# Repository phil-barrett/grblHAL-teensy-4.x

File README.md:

# grbl-teensy-4
GRBL Breakout Boards for Teensy 4.x Uses the [grblHAL Teensy 4 version](https://github.com/grblHAL/iMXRT1062).
# Resources for grblHAL, T41U5XBB and related CNC topics
[Resources](https://www.grbl.org/resources)

## Nov 12, 2025.  V2.20 is now available.
Upgraded to AHCT drivers.
Upgraded to EL3H7 optoisolators.
Added board level configuration to support spindle sync. See [user manual](https://github.com/phil-barrett/grblHAL-teensy-4.x/blob/master/T41U5XBB%20User%20Manual.pdf) for details.
.

[Available for purchase on my store.](https://brookwood-design-77.myshopify.com/)

## Aug 20, 2025.  V2.10 is now available.
Trimmer potentiometer moved onto PCB, unneeded features removed and some cosmetic changes.  Now using KiCAD instead of Eagle. V2.11 is coming but is functionally the same as V2.10 (minor slik screen changes).  [User Manual](https://github.com/phil-barrett/grblHAL-teensy-4.x/blob/master/T41U5XBB%20User%20Manual.pdf) updated. 

## Oct 15, 2020.  V2.09 is now available.
A small number of changes, mostly cosmetic. Also added mounting holes for I2C and Serial I/O daughter boards. 

## Sept 29, 2020. Ethernet Support Added
grblHAL support for Ethernet is now pretty solid.  I have updated the [User Manual](https://github.com/phil-barrett/grblHAL-teensy-4.x/blob/master/T41U5XBB%20v207.pdf) to include instructions on using Ethernet. 

## June 28, 2020. New Versions!
I have finished 2 new 5 axis versions based on the Teensy 4.1. One supports an Ethernet interface and the other supports a USB interface. I will be making a few "Unkit" boards avalable. These have all the surface mount components installed (with the execption of the EEPROM IC). Teensy 4.1 not included. 

The "Unkit" board.

T41U5XBB - Fully populated USB based version.  

T41E5XBB - Fully populated Ethernet version

Lots of new features!
## Features
  * 5 Axis control outputs – 5V compatible.
  * Independent enables for each axis.
  * 10 Opto-isolated inputs including standard GRBL controls and limits switches for all axes.
  * 7 Relay Outputs – Spindle, Mist Coolant, Flood Coolant, Dust Collector and 3 auxiliary relays. Each output can control a relay coil directly or 5V TTL (SSR compatible) devices.
  * Dust Extraction relay support. Activated by spindle enable.
  * Separate control of Dust Collector relay via pin header.
  * Relay coil voltage switchable between 5V and 12V. 
  * Standard GRBL spindle control outputs – 5V compliant.
  * 0-10V spindle control output.
  * Screw Terminals for reliable connections available for most I/O.
  * 4 Digital Inputs – EMI protected, 15.9KHz low pass filter, Schmitt Trigger.
  * I2C header.
  * EEPROM footprint for SOIC8 devices.
  * LED indicators for 5V and 12V.
  * USB interface.
  * Ethernet interface. (T41E5XBB only)
  * Serial I/O Header

## Firmware
Prebuilt versions of grblHAL are available to directly load into the Teensy 4.1 [Follow the instructions here.](https://github.com/phil-barrett/grblHAL-teensy-4.x/blob/master/prebuilt.md)

## Documentation
### Schematic
The two versions currently share a common schematic and PCB layout. This may not be the case in the future. [Schematic is here.](https://github.com/phil-barrett/grbl-teensy-4/blob/master/v2.07%20schematic.pdf)

### Manual
The [User Manual is available here.](https://github.com/phil-barrett/grbl-teensy-4/blob/master/T41U5XBB%20v207.pdf)

### Bare PCB from OSHPark
[Available here](https://oshpark.com/shared_projects/QWr3OZUe) This is fairly expensive. For a less costly approach, you can use the Gerber files below to order from more cost effective fabs.

### Gerbers
[Gerbers are available here.](https://github.com/phil-barrett/grbl-teensy-4/blob/master/teensy%204.1x207.zip) Board size is 85 x 96 mm, 2 layer, 1.6 mm thickness.

### Build Guide
A brief guide to building grblHAL from source [for the breakout board is here](https://github.com/phil-barrett/grbl-teensy-4/blob/master/grblHAL%20Build%20Guide.pdf).

## Previous Version

## Features:
  * 4 Axis control outputs – 5V Compatible.
  * 8 Opto-isolated inputs.
  * Full spindle control outputs – 5V compatible.
  * 0-10V spindle control output.
  * 7 Relay Outputs.
  * Relay voltage switchable between 5V and 12V. 
  * Dust Extraction relay output slaved to spindle.
  * Screw Terminal I/O for reliable connections.
  * I2C header.
  * EEPROM footprint for SOIC8 devices.
  * LED indicators for 5V and 12V.

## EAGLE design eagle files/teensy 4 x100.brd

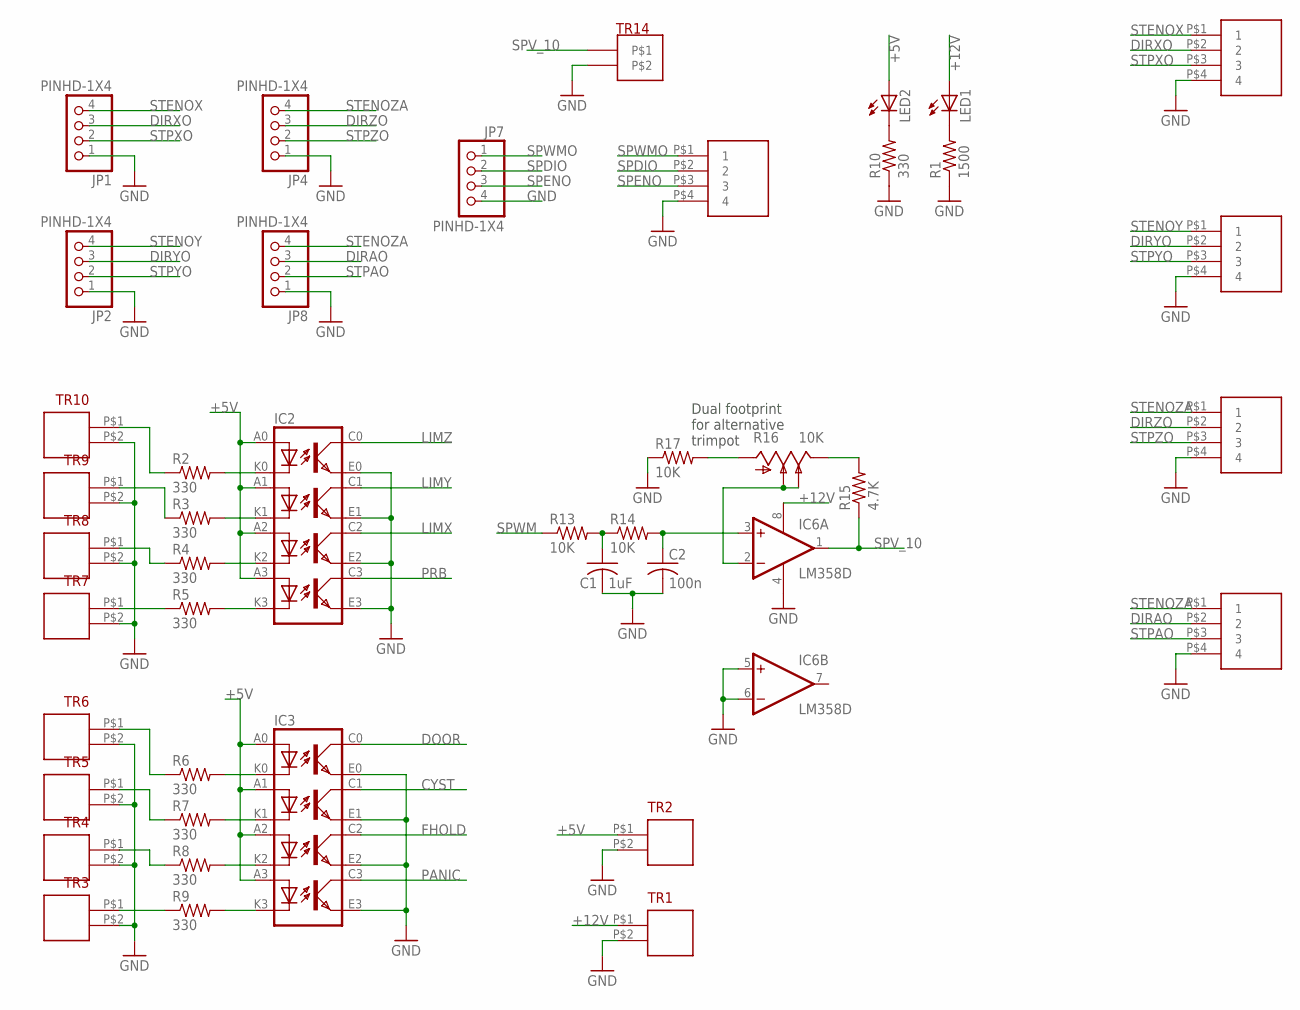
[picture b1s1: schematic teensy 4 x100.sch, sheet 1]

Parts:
C1: 1uF; C1206
C2: 100n; C1206
IC2, IC3: LTV846S; DIL16-SMD
IC6: LM358D; SO08
JP1, JP2, JP4, JP7, JP8: PINHD-1X4; 1X04
LED1, LED2: LED3MM
R1: 1500; R1206
R2, R3, R4, R5, R6, R7, R8, R9, R10: 330; R1206
R13, R14, R17: 10K; R1206
R15: 4.7K; R1206
R16: 10K; B64Y
TR1, TR2, TR3, TR4, TR5, TR6, TR7, TR8, TR9, TR10, TR14: T35-2
TR11, TR12, TR13, TR19, TR20: T35-4

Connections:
+5V: IC2.A0, IC2.A1, IC2.A2, IC2.A3, IC3.A0, IC3.A1, IC3.A2, IC3.A3, LED2.A, TR2.P$1; also elsewhere on the board
+12V: IC6.8 (V+), LED1.A, TR1.P$1; also elsewhere on the board
CYST: IC3.C1 (COL1); also elsewhere on the board
DIRAO: JP8.3, TR20.P$2 (2); also elsewhere on the board
DIRXO: JP1.3, TR11.P$2 (2); also elsewhere on the board
DIRYO: JP2.3, TR12.P$2 (2); also elsewhere on the board
DIRZO: JP4.3, TR13.P$2 (2); also elsewhere on the board
DOOR: IC3.C0 (COL0); also elsewhere on the board
FHOLD: IC3.C2 (COL2); also elsewhere on the board
GND: C1.2, C2.2, IC2.E0 (EMIT0), IC2.E1 (EMIT1), IC2.E2 (EMIT2), IC2.E3 (EMIT3), IC3.E0 (EMIT0), IC3.E1 (EMIT1), IC3.E2 (EMIT2), IC3.E3 (EMIT3), IC6.4 (V-), IC6.5 (+IN), IC6.6 (-IN), JP1.1, JP2.1, JP4.1, JP7.4, JP8.1, R1.1, R10.1, R17.1, TR1.P$2, TR2.P$2, TR3.P$2, TR4.P$2, TR5.P$2, TR6.P$2, TR7.P$2, TR8.P$2, TR9.P$2, TR10.P$2, TR11.P$4 (4), TR12.P$4 (4), TR13.P$4 (4), TR14.P$2, TR19.P$4 (4), TR20.P$4 (4); also elsewhere on the board
LIMX: IC2.C2 (COL2); also elsewhere on the board
LIMY: IC2.C1 (COL1); also elsewhere on the board
LIMZ: IC2.C0 (COL0); also elsewhere on the board
unnamed: IC3.K0 (C0), R6.2
unnamed: LED2.K (C), R10.2
unnamed: IC3.K1 (C1), R7.2
unnamed: LED1.K (C), R1.2
unnamed: IC3.K2 (C2), R8.2
unnamed: IC2.K0 (C0), R2.2
unnamed: IC2.K1 (C1), R3.2
unnamed: IC2.K2 (C2), R4.2
unnamed: IC2.K3 (C3), R5.2
unnamed: IC3.K3 (C3), R9.2
unnamed: C1.1, R13.2, R14.1
unnamed: C2.1, IC6.3 (+IN), R14.2
unnamed: R15.2, R16.E
unnamed: IC6.2 (-IN), R16.S, R16.S1
unnamed: R16.A, R17.2
unnamed: R2.1, TR10.P$1
unnamed: R3.1, TR9.P$1
unnamed: R4.1, TR8.P$1
unnamed: R5.1, TR7.P$1
unnamed: R6.1, TR6.P$1
unnamed: R7.1, TR5.P$1
unnamed: R8.1, TR4.P$1
unnamed: R9.1, TR3.P$1
PANIC: IC3.C3 (COL3); also elsewhere on the board
PRB: IC2.C3 (COL3); also elsewhere on the board
SPDIO: JP7.2, TR19.P$2 (2); also elsewhere on the board
SPENO: JP7.3, TR19.P$3 (3); also elsewhere on the board
SPV_10: IC6.1 (OUT), R15.1, TR14.P$1
SPWM: R13.1; also elsewhere on the board
SPWMO: JP7.1, TR19.P$1 (1); also elsewhere on the board
STENOX: JP1.4, TR11.P$1 (1); also elsewhere on the board
STENOY: JP2.4, TR12.P$1 (1); also elsewhere on the board
STENOZA: JP4.4, JP8.4, TR13.P$1 (1), TR20.P$1 (1); also elsewhere on the board
STPAO: JP8.2, TR20.P$3 (3); also elsewhere on the board
STPXO: JP1.2, TR11.P$3 (3); also elsewhere on the board
STPYO: JP2.2, TR12.P$3 (3); also elsewhere on the board
STPZO: JP4.2, TR13.P$3 (3); also elsewhere on the board

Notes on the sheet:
Dual footprint for alternative trimpot

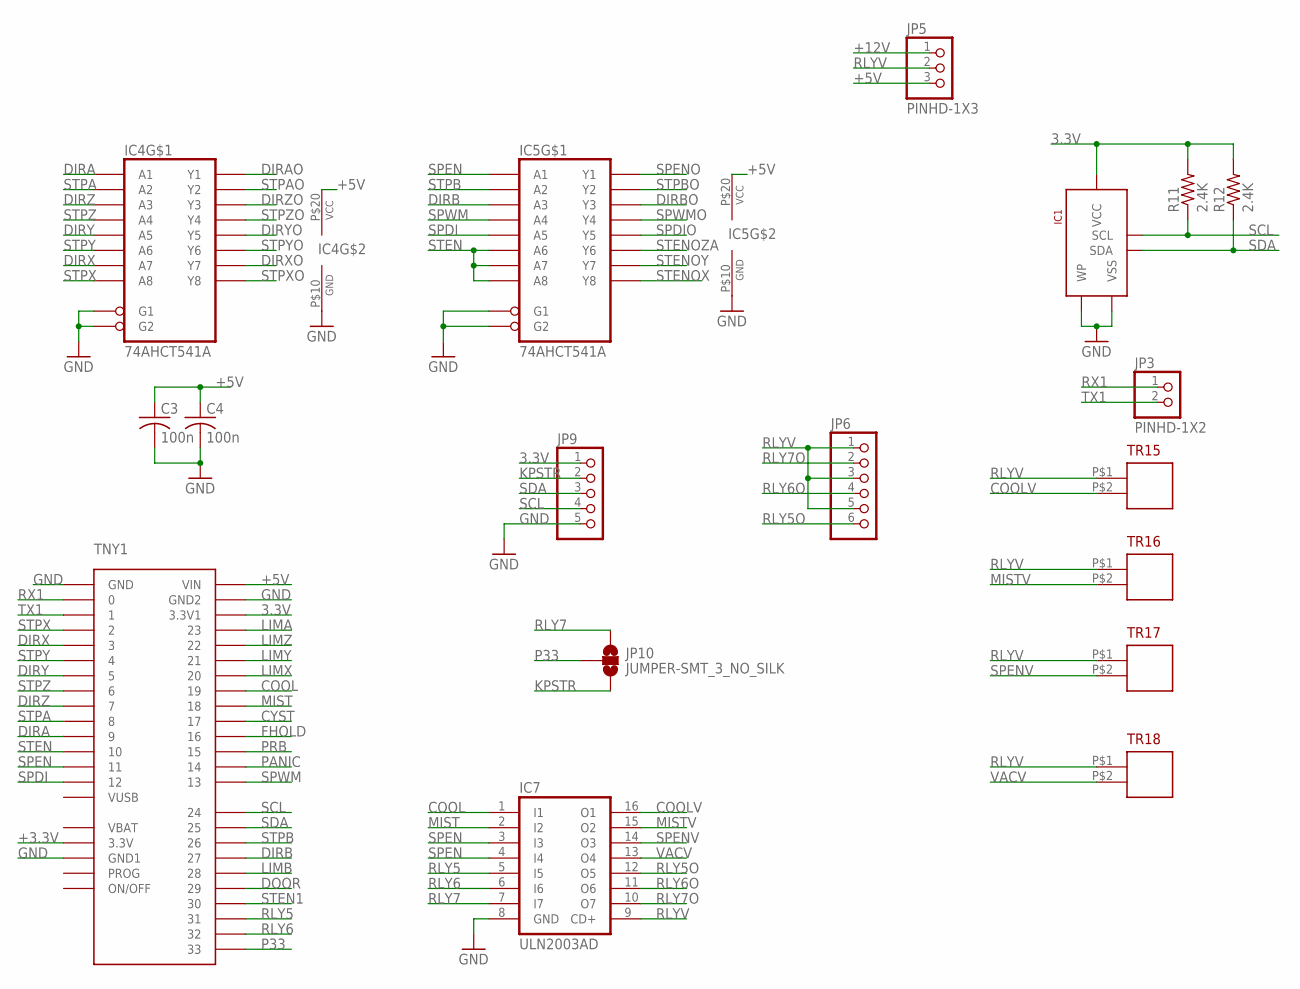
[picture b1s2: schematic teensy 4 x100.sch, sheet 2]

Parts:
C3, C4: 100n; C1206
IC1: 24LCxxx; SOIC-8(MICROCHIP)
IC4, IC5: 74AHCT541A; TSSOP20
IC7: ULN2003AD; SO16
JP3: PINHD-1X2; 1X02
JP5: PINHD-1X3; 1X03
JP6: PINHD-1X6; 1X06
JP9: PINHD-1X5; 1X05
JP10: JUMPER-SMT_3_NO_SILK; SMT-JUMPER_3_NO_SILK
R11, R12: 2.4K; R1206
TNY1: TEENSY4.0
TR15, TR16, TR17, TR18: T35-2

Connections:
3.3V: IC1.P$8 (VCC), JP9.1, R11.2, R12.2, TNY1.3.31 (3.3V1)
+3.3V: TNY1.3.30 (3.3V)
+5V: C3.1, C4.1, IC4.P$20 (VCC), IC5.P$20 (VCC), JP5.3, TNY1.VIN; also elsewhere on the board
+12V: JP5.1; also elsewhere on the board
COOL: IC7.1 (I1), TNY1.19
COOLV: IC7.16 (O1), TR15.P$2
CYST: TNY1.17; also elsewhere on the board
DIRA: IC4.P$2 (A1), TNY1.9
DIRAO: IC4.P$18 (Y1); also elsewhere on the board
DIRB: IC5.P$4 (A3), TNY1.27
DIRBO: IC5.P$16 (Y3)
DIRX: IC4.P$8 (A7), TNY1.3
DIRXO: IC4.P$12 (Y7); also elsewhere on the board
DIRY: IC4.P$6 (A5), TNY1.5
DIRYO: IC4.P$14 (Y5); also elsewhere on the board
DIRZ: IC4.P$4 (A3), TNY1.7
DIRZO: IC4.P$16 (Y3); also elsewhere on the board
DOOR: TNY1.29; also elsewhere on the board
FHOLD: TNY1.16; also elsewhere on the board
GND: C3.2, C4.2, IC1.P$4 (VSS), IC1.P$7 (WP), IC4.P$1 (G1), IC4.P$10 (GND), IC4.P$19 (G2), IC5.P$1 (G1), IC5.P$10 (GND), IC5.P$19 (G2), IC7.8 (GND), JP9.5, TNY1.GND, TNY1.GND1, TNY1.GND2; also elsewhere on the board
KPSTR: JP9.2, JP10.3
LIMA: TNY1.23
LIMB: TNY1.28
LIMX: TNY1.20; also elsewhere on the board
LIMY: TNY1.21; also elsewhere on the board
LIMZ: TNY1.22; also elsewhere on the board
MIST: IC7.2 (I2), TNY1.18
MISTV: IC7.15 (O2), TR16.P$2
P33: JP10.2, TNY1.33
PANIC: TNY1.14; also elsewhere on the board
PRB: TNY1.15; also elsewhere on the board
RLY5: IC7.5 (I5), TNY1.31
RLY5O: IC7.12 (O5), JP6.6
RLY6: IC7.6 (I6), TNY1.32
RLY6O: IC7.11 (O6), JP6.4
RLY7: IC7.7 (I7), JP10.1
RLY7O: IC7.10 (O7), JP6.2
RLYV: IC7.9 (CD+), JP5.2, JP6.1, JP6.3, JP6.5, TR15.P$1, TR16.P$1, TR17.P$1, TR18.P$1
RX1: JP3.1, TNY1.0
SCL: IC1.P$6 (SCL), JP9.4, R11.1, TNY1.24
SDA: IC1.P$5 (SDA), JP9.3, R12.1, TNY1.25
SPDI: IC5.P$6 (A5), TNY1.12
SPDIO: IC5.P$14 (Y5); also elsewhere on the board
SPEN: IC5.P$2 (A1), IC7.3 (I3), IC7.4 (I4), TNY1.11
SPENO: IC5.P$18 (Y1); also elsewhere on the board
SPENV: IC7.14 (O3), TR17.P$2
SPWM: IC5.P$5 (A4), TNY1.13; also elsewhere on the board
SPWMO: IC5.P$15 (Y4); also elsewhere on the board
STEN: IC5.P$7 (A6), IC5.P$8 (A7), IC5.P$9 (A8), TNY1.10
STEN1: TNY1.30
STENOX: IC5.P$11 (Y8); also elsewhere on the board
STENOY: IC5.P$12 (Y7); also elsewhere on the board
STENOZA: IC5.P$13 (Y6); also elsewhere on the board
STPA: IC4.P$3 (A2), TNY1.8
STPAO: IC4.P$17 (Y2); also elsewhere on the board
STPB: IC5.P$3 (A2), TNY1.26
STPBO: IC5.P$17 (Y2)
STPX: IC4.P$9 (A8), TNY1.2
STPXO: IC4.P$11 (Y8); also elsewhere on the board
STPY: IC4.P$7 (A6), TNY1.4
STPYO: IC4.P$13 (Y6); also elsewhere on the board
STPZ: IC4.P$5 (A4), TNY1.6
STPZO: IC4.P$15 (Y4); also elsewhere on the board
TX1: JP3.2, TNY1.1
VACV: IC7.13 (O4), TR18.P$2

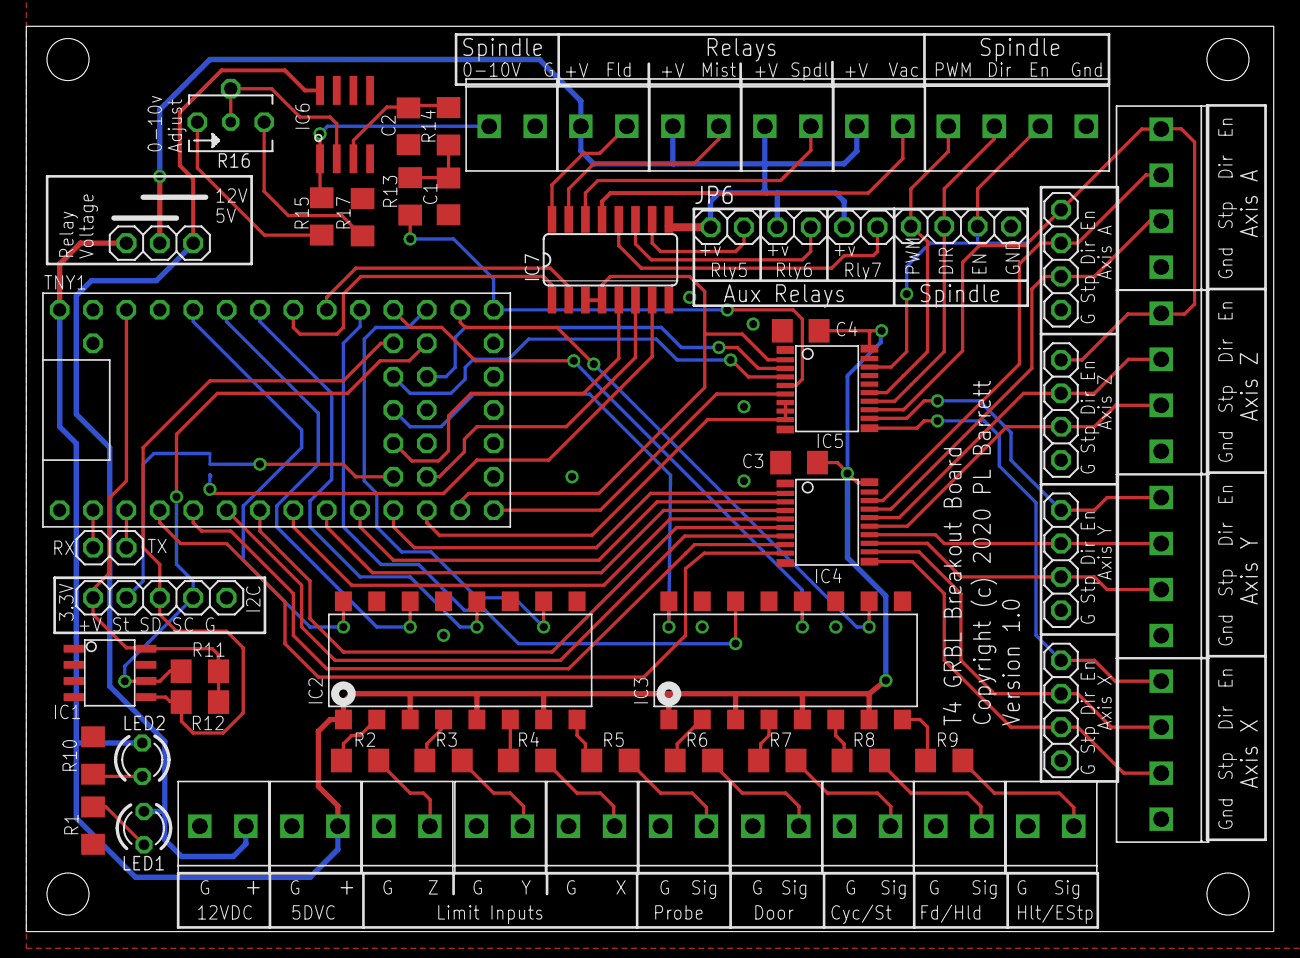
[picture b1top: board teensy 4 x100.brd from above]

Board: 2 copper layers, 94.9 x 68.9 mm, 61 parts (1 on the bottom side), 83 nets.

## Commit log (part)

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2020-02-18 Added schematic
2020-02-18 added eagle sch and brd files
2020-02-19 Add files via upload
    fix to stepper enable lines
2020-02-19 Add files via upload
    Added i2c header and a few trace cleanups.
2020-02-19 Add files via upload
    Added i2c header, trace clean up.
2020-02-19 Add files via upload
    PCB traces. Red is top, blue is bottom.
2020-02-19 Add files via upload
    Ver .2 Made alternate pin assignments more clear in the table. Swapped Spindle PWM and Spindle Enable pins to put PWM on the LED pin for a visual spindle diagnostic.
2020-02-20 Add files via upload
    Minor changes to Spindle pin assignments.
2020-02-20 Add files via upload
    Changed spindle pin assignments, in line with the Teensy 4 Pinouts PDF
2020-02-20 Add files via upload
    Depreciating this document.
2020-02-20 Add files via upload
    Update circuit to reflect moving spindle PWM to pin 13 and Spindle enable to Pin 12.
2020-03-01 Delete teensy 4 x100.csv
    replacing with official BOM
2020-03-07 Photo of V1.00 board
2020-03-07 Add files via upload
    resized smaller
2020-06-28 Add files via upload
    New version based on Teensy 4.1.
2020-07-06 Add files via upload
    Updated installation instructions
2020-07-06 Add files via upload
    Updated Firmware information and general edits.
2020-07-06 Add V2.05 Schematic
    V2.05 Schematic.
2020-07-06 Build Guide, initial commit
2020-07-06 Update for grblHAL build guide
2020-07-06 updated for build guide reference
2020-07-08 update. fixed errors and added configurations
2020-07-10 initial committ
2020-07-10 First "real" commit.
2020-07-10 added links to firmware loading instructions
2020-07-15 t4.1 library initial commit
2020-07-21 added compatibility configurations
2020-07-29 Update to include info on cloning the A Axis from Y.
2020-08-04 Minor edits
2020-08-19 dust extractor boot for DW611 router.
2020-09-29 Update to include Ethernet instructions.
2020-09-29 Fixed typos and added some minor clarifications.
2020-10-15 V2.09 photo w/coin
2020-10-15 V2.09 photo
2020-10-27 Updated incorrect 24 pin socket part number.
2020-11-08 Ethernet Configurations
    TEENSY41_3X_ETH_ENC.hex --- 3 Axis, ethernet, encoder.
    TEENSY41_3XGY_ETH_ENC.hex --- 3 Axis, B Axis ganged to Y, ethernet, encoder.
    TEENSY41_4X_ETH_ENC.hex --- 4 Axis, ethernet, encoder.
    TEENSY41_4XGY_ETH_ENC.hex --- 4 Axis, B Axis ganged to Y, ethernet, encoder.
    TEENSY41_5X_ETH_ENC.hex --- 5 Axis, ethernet, encoder.
2020-11-09 updated ethernet configurations.
2020-11-09 Added ethernet information.
2020-11-09 minor update.
2020-11-19 GCode test cases. Initial committ
2020-11-20 Minor name tweak
2020-11-20 Updated assembly info for Ethernet
2020-12-01 Added 2x3 2mm socket and header part numbers
2021-01-29 updated builds, fix startup problem
2021-02-10 grblHAL binaries with planning buffer increase to 1024.
2021-02-12 updated build infomation.
2021-02-12 Depreciated in favor grblHAL Wiki
2021-02-12 Updated to include information about the lwIP Ethernet library.
2021-02-24 Eagle Schematic for V2.09.
2021-10-21 Add files via upload
    T41U5XBB binary. 4 Axis, Y ganged with B, Ethernet enabled, no Auto-square.
2021-10-31 Latest version of T41 hex files.
    See the read me for naming conventions. Contact me directly if you need one that is not included. Phil.
2021-12-02 Replaced grblHAL_T41E3XGYAS.hex with correct number of axes
2021-12-03 Upload to resolve corrupt zip file issue
2021-12-17 T41U5XBB V 2.09 STEP file - experimental.
    KiCAD import, used to generate STEP file. Not verified.
2022-01-03 updated for new configurations and added options
2022-01-03 Updated configurations.
2022-01-03 Updated to newer builds of grblHAL
2022-10-11 Add files via upload
    Teensy 4.0 breakout board.
2023-01-27 Add files via upload
    Common T41U5XBB firmware configuration files for use with the grblHAL Web Builder.
2025-08-20 Add files via upload
    Updated manual to include V2.10 and V2.11 versions.
2025-09-16 Add files via upload
    Update to clarify Link A Axis to Y usage.

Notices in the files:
eagle files/teensy 4 x100.brd:
Copyright (c) 2020 PL Barrett
